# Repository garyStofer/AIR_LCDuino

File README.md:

# AIR_LCDuino
~Uino based LCD display instrument to indicate Atmosphere and Wind related measurements. 

This Arduino-IDE based project is for a simple Air-data display (Weather station) display based on a custom ATMEGA 328P based PCB which incorporates a standard 8x2 LCD (HD44780) and a rotary knob to select the various readings and settings. 

The sensors used are the Air-data and Wind sensors from the Wunder-Weather-Station project and can be found here [http://wws.us.to](http://wws.us.to)

The EagleCAD files for the PCB can be found in the hardware folder. The base PCB can be ordered from OSH PCB by searching for [Air_LCDuino](https://oshpark.com/shared_projects/kT6TDwLU) under shared Projects.

The instrument PCB and housing uses a 2.25" standard aircraft round instrument hole pattern. The CAD files for a CNC routed enclosure can be found in the mechanical folder. You will need a copy of CamBam software to open the .cb source file, but the G-code .ngc file should run on most CNC routers with minor modification. There is a .dxf file that shows the basic dims of the PCB and LCD stack-up. 

The following readings are displayed:
- Bus Voltage 
- Density Altitude
- Standard Altitude (Standard Atmosphere)
- Compensated Altitude (by entering current sea level pressure)
- Station Pressure
- Humidity %RH
- Temperature
- Dew point
- Temperature Dewpt. Spread 
- Wind Direction
- Wind Speed current ( 1 second)
- Wind Average (10 minutes running average)
- Wind Gust ( last 10 minutes )

The two LEDs indicate alarm situations 

Blue LED comes on when Temp <= 1deg C
Red LED comes on when Vbus is < 11 or >15 volt 
Red LED comes on when Temp-Dewpt spread is <8 deg F

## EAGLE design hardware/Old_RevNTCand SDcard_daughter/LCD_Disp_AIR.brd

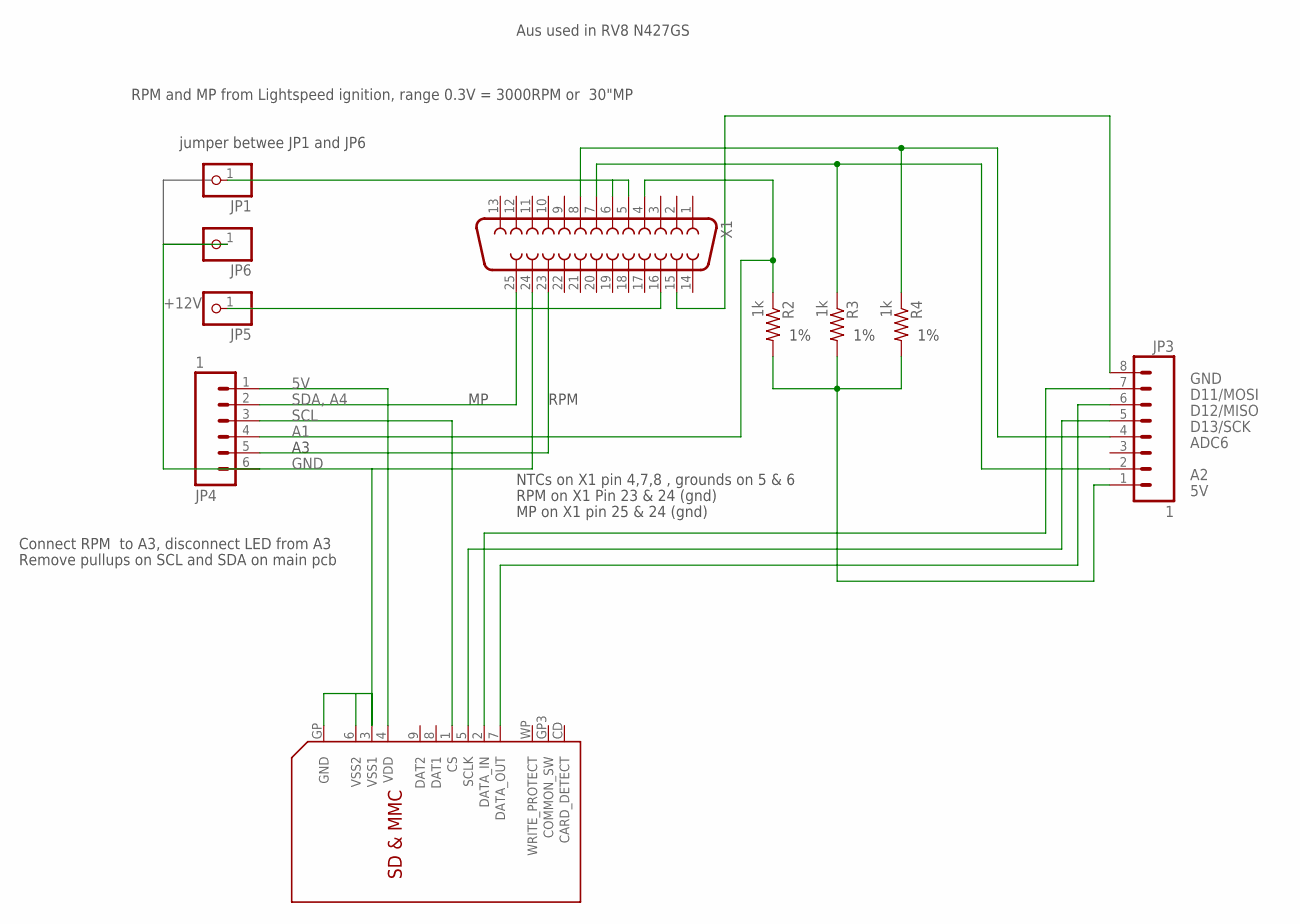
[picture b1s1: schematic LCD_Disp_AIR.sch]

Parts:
JP1, JP6: PINHD-1X1CB; 1X01-CLEANBIG
JP3: 1; 1X08
JP4: 1; 1X06
JP5: PINHD-1X1; 1X01
R2, R3, R4: 1k; 0204/7
U$1: SDMMC06132; 06132
X1: DB25_FEMALEVB; F25VB

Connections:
+12V: JP5.1, X1.16
GND: JP4.6, JP6.1, U$1.3 (VSS1), U$1.6 (VSS2), U$1.GP (GND), X1.24
MISO: JP3.6, U$1.7 (DATA_OUT)
MOSI: JP3.7, U$1.2 (DATA_IN)
unnamed: JP1.1, X1.5, X1.6
unnamed: JP3.1, R2.2, R3.2, R4.2
unnamed: JP3.8, X1.15
unnamed: JP4.5, X1.23
unnamed: JP4.2, X1.25
unnamed: JP3.2, R3.1, X1.7
unnamed: JP3.4, R4.1, X1.8
unnamed: JP4.4, R2.1, X1.4
SCI_SD_SS: JP4.3, U$1.1 (CS)
SCLK: JP3.5, U$1.5 (SCLK)
VDD: JP4.1, U$1.4 (VDD)

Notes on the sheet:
SDA, A4
SCL
GND
ADC6
D13/SCK
D12/MISO
D11/MOSI
jumper betwee JP1 and JP6
Connect RPM to A3, disconnect LED from A3
Remove pullups on SCL and SDA on main pcb
RPM
RPM and MP from Lightspeed ignition, range 0.3V = 3000RPM or 30"MP
Aus used in RV8 N427GS
NTCs on X1 pin 4,7,8 , grounds on 5 & 6
RPM on X1 Pin 23 & 24 (gnd)
MP on X1 pin 25 & 24 (gnd)

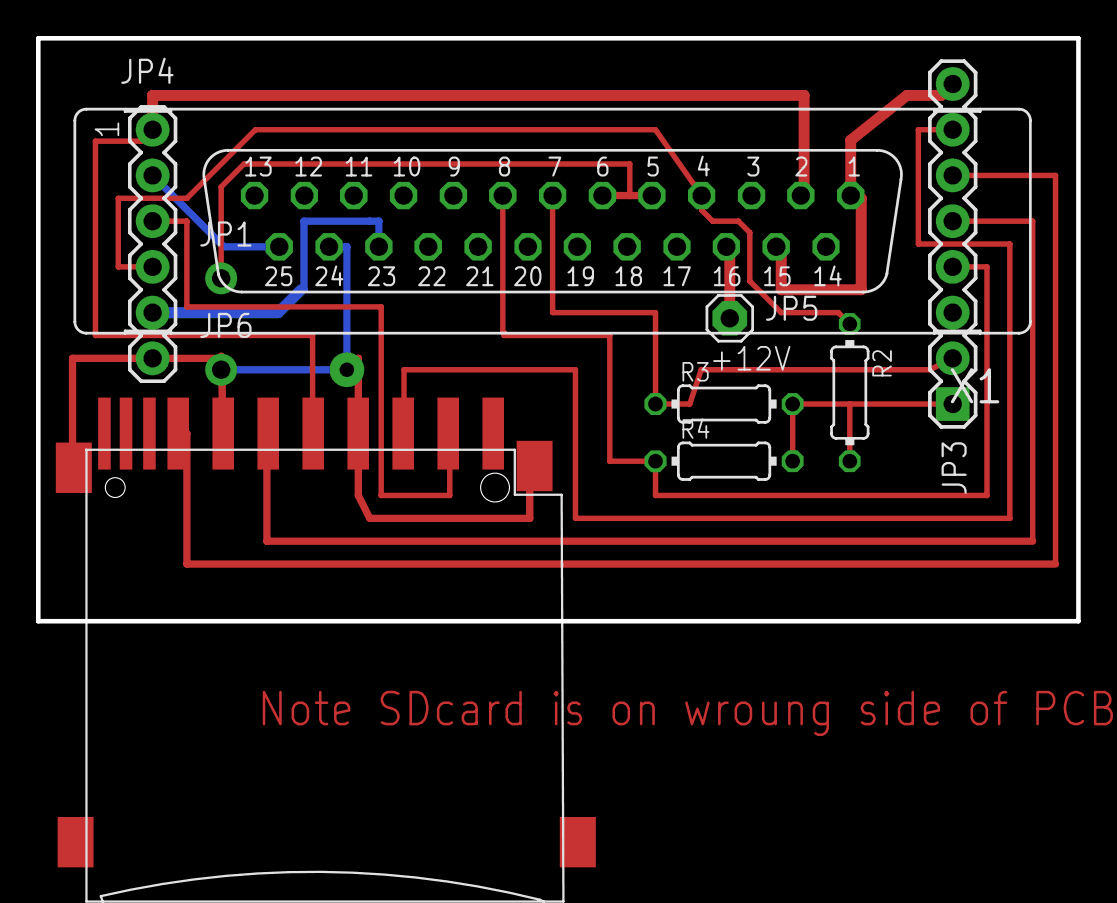
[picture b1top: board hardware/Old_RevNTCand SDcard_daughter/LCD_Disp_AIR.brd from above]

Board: 2 copper layers, 57.8 x 32.4 mm, 10 parts (0 on the bottom side), 15 nets.

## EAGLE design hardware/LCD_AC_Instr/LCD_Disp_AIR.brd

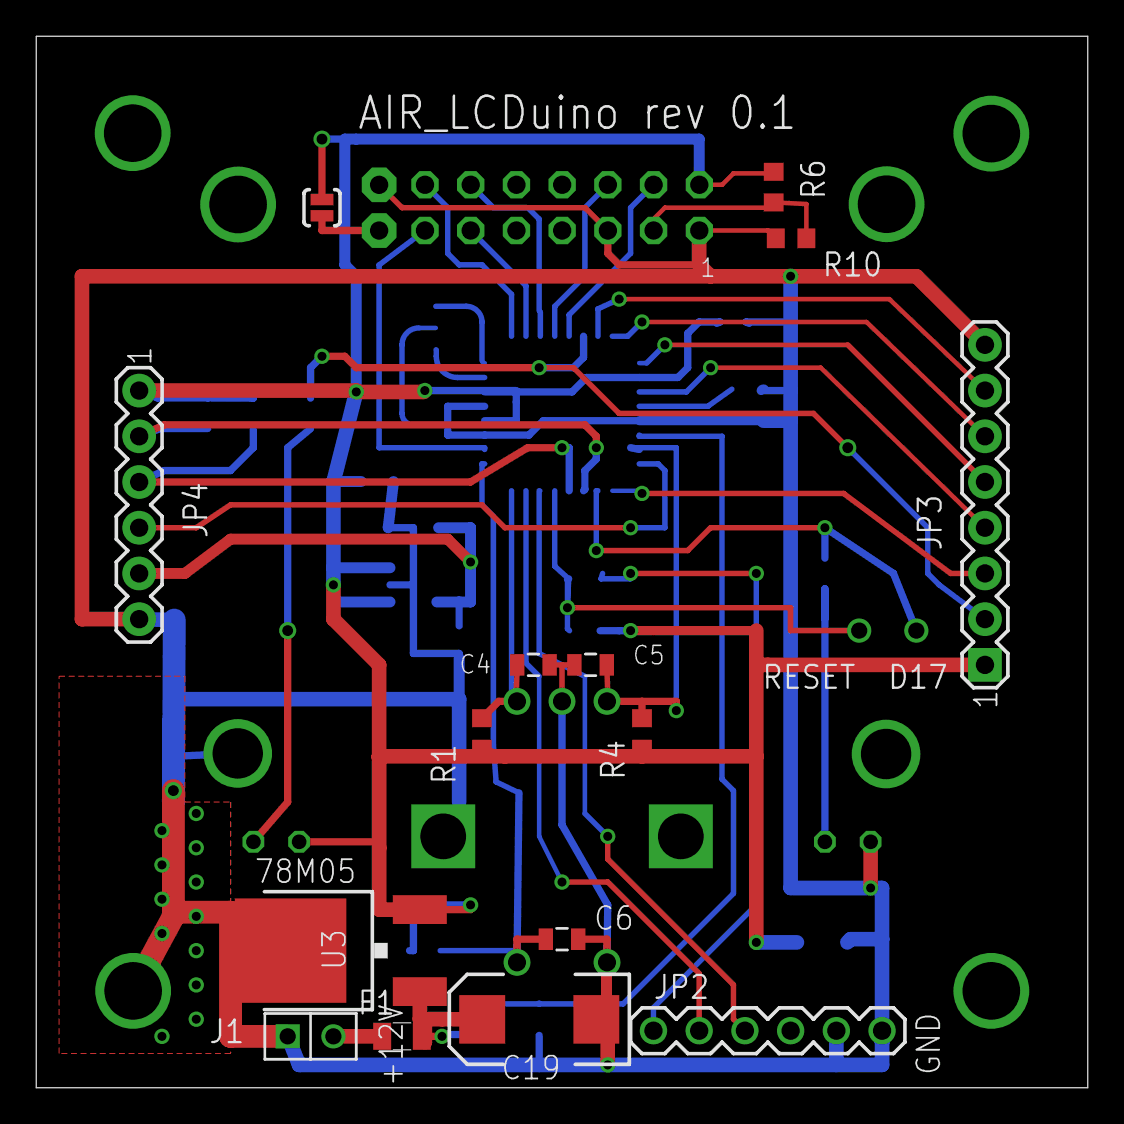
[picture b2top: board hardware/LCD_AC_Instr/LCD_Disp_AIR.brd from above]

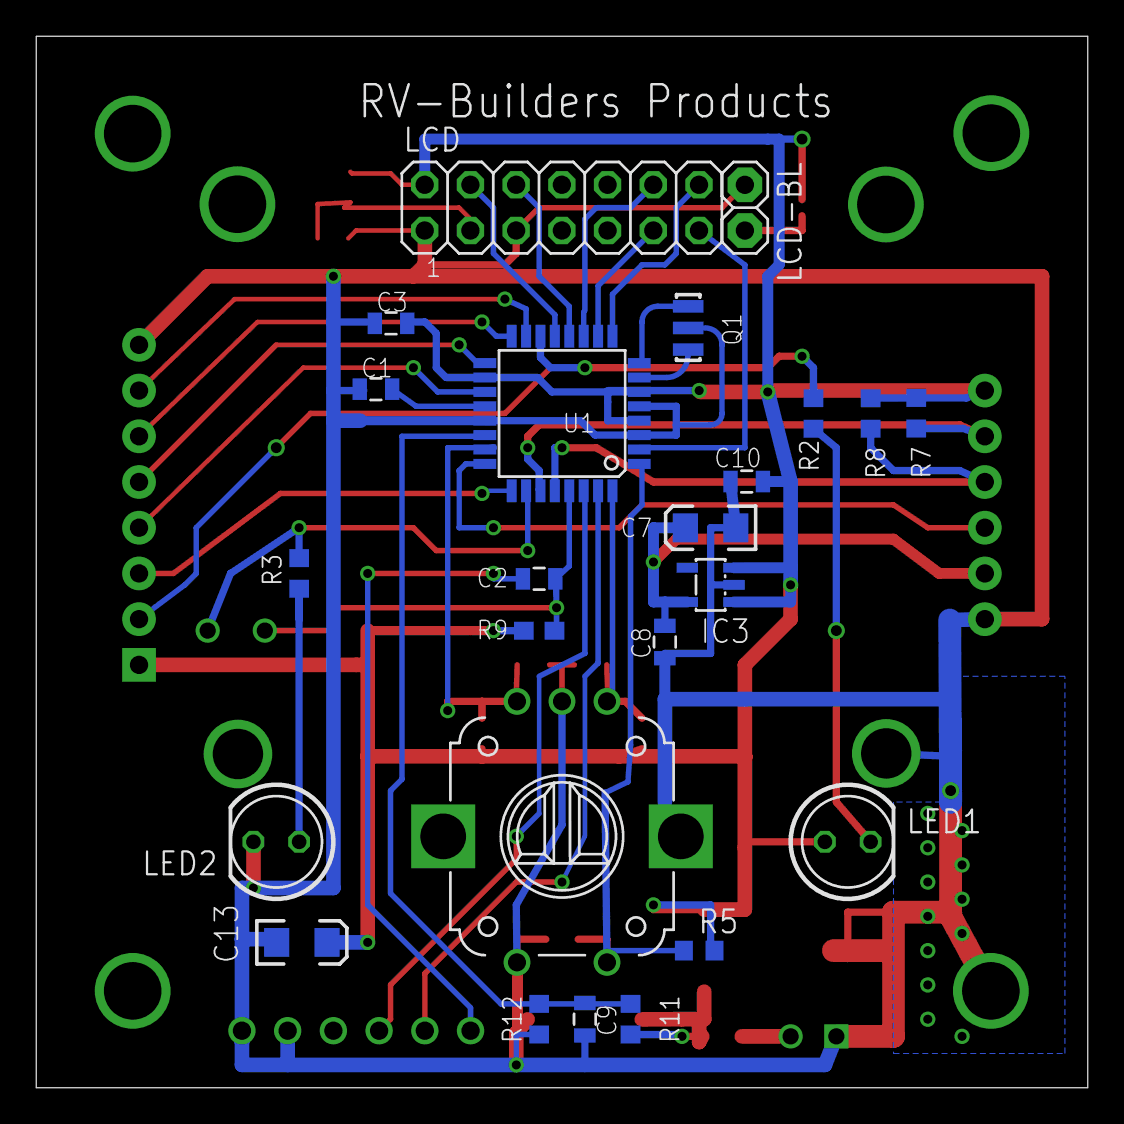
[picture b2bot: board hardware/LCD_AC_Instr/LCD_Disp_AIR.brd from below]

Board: 2 copper layers, 58.4 x 58.4 mm, 41 parts (24 on the bottom side), 36 nets.

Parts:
C1, C2, C3, C4, C5, C6, C8, C9, C10: 0.1uF; 0805
C7, C13: 10uF; EIA3216
C19: 10uF; EIA7343
D17: D17-A3-PC3; P1-13
F1: 4A; PTC0805
IC3: TC10553.3V; SOT23-5
J1: 12V input; M1X2
JP2: 5V UART; 1X06
JP3: 1; 1X08
JP4: 1; 1X06
LCD: LCD; 2X07
LCD-BL: 1X02
LED1, LED2: LED-5MM
Q1: 16MHz; RESONATOR-SMD
R1, R4, R5: 10k; R603
R2, R3: 470; R603
R6: R603
R7, R8: 100k; R603
R9: 10K; 0603
R10: 120; R603
R11: 14K; R603
R12: 6.8K; R603
RESET: SOLDER_POINTA; P1-13
SJ1: BACKLIGHT; SJ_2S-NO
SW1: ENCODER_SW1-PEC12; PEC12_INCREMENTAL_ENCODER
U1: ATMEGA328P-AU(R); TQFP32-08
U3: 78M05; DPACK

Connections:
5V: C3.2, C10.1, C13.A, IC3.1, IC3.3, JP3.1, JP4.1, LCD.2, LED1.A, R1.2, R4.1, R5.2, R6.2, R7.1, R8.1, R9.2, SJ1.1, U1.4, U1.6, U1.18, U3.3
12V_INPUT: C19.A, F1.2, R11.2, U3.1
A0_PC0: C5.2, R4.2, SW1.B, U1.23
A1_PC1: JP4.4, U1.24
A2_PC2: JP3.3, U1.25
A3_PC3: D17.1, R3.2, U1.26
A4_PC4_SDA: JP4.2, R7.2, U1.27
A5_PC5_SCL: JP4.3, R8.2, U1.28
ADC6: JP3.4, U1.19
ADC7: C9.1, R11.1, R12.2, U1.22
AREF: C1.2, U1.20
D2_PD2(INT0): C4.2, R1.1, SW1.A, U1.32
D3_PD3(INT1): C6.2, R5.1, SW1.P1, U1.1
D4_PD4: LCD.13, U1.2
D5_PD5: LCD.14, U1.9
D6_PD6: LCD.11, U1.10
D7_PD7: LCD.12, U1.11
D8_PB0: LCD.6, U1.12
D9_PB1: LCD.4, U1.13
D10_PB2_SS: JP3.2, R2.2, U1.14
D11_PB3_MOSI: JP3.7, U1.15
D12_PB4_MISO: JP3.6, U1.16
D13_PB5_SCK: JP3.5, U1.17
GND: C1.1, C3.1, C4.1, C5.1, C6.1, C7.C, C8.2, C9.2, C10.2, C13.C, C19.C, IC3.2, J1.1, JP2.5, JP2.6, JP3.8, JP4.6, LCD.1, LCD.5, LCD-BL.1, LED2.K, Q1.2, R10.1, R12.1, SW1.C, SW1.P2, U1.3, U1.5, U1.21, U3.4
unnamed: LCD.3, R6.1, R10.2
unnamed: Q1.1, U1.8
unnamed: C2.2, JP2.1
unnamed: Q1.3, U1.7
unnamed: F1.1, J1.2
unnamed: LED1.K, R2.1
unnamed: LCD-BL.2, SJ1.2
unnamed: LED2.A, R3.1
RESET: C2.1, R9.1, RESET.1, U1.29
RXI: JP2.3, U1.30
TXO: JP2.2, U1.31
V3_3V: C7.A, C8.1, IC3.5, JP4.5

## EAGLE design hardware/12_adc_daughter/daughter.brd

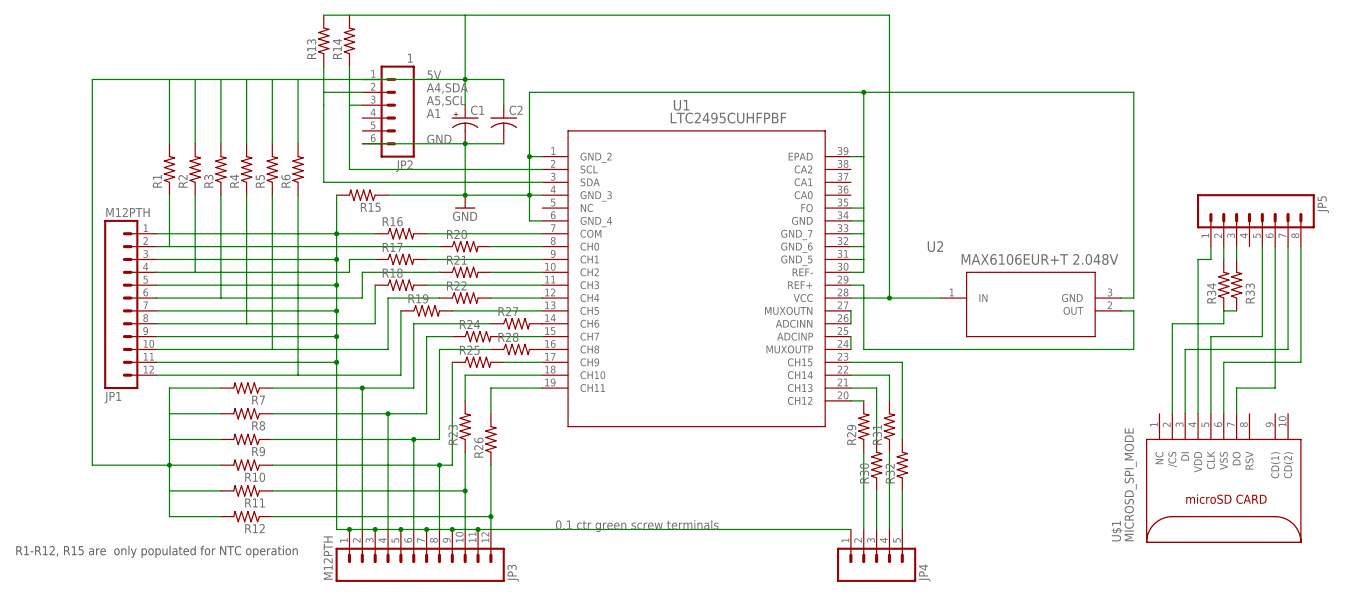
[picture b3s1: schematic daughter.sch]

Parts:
C1: CPOL-USSMCB; SMC_B
C2: C-USC0805; C0805
JP1, JP3: M12PTH; 1X12
JP2: 1; 1X06
JP4: M05PTH; 1X05
JP5: M081X08; 1X08
R1, R2, R3, R4, R5, R6, R7, R8, R9, R10, R11, R12, R13, R14, R15, R16, R17, R18, R19, R20, R21, R22, R23, R24, R25, R26, R27, R28, R29, R30, R31, R32, R33, R34: R-US_R0603; R0603
U1: LTC2495CUHFPBF; QFN-38_UHF
U2: MAX6106EUR+T 2.048V; 21-0051H
U$1: MICROSD_SPI_MODE; MICRO_SD_CONNECTOR

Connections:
GND: C1.-, C2.2, JP2.6, R15.1, U1.1 (GND_2), U1.4 (GND_3), U1.6 (GND_4), U1.30 (REF-), U1.31 (GND_5), U1.32 (GND_6), U1.33 (GND_7), U1.34 (GND), U1.35 (FO), U1.39 (EPAD), U2.3 (GND)
unnamed: JP1.2, R1.1, R20.1
unnamed: JP1.1, JP1.3, JP1.5, JP1.7, JP1.9, JP1.11, JP3.1, JP3.3, JP3.5, JP3.7, JP3.9, JP3.11, JP4.1, R15.2, R16.1
unnamed: JP1.4, R2.1, R17.1
unnamed: JP1.6, R3.1, R21.1
unnamed: JP5.5, U$1.5 (CLK)
unnamed: JP1.8, R4.1, R18.1
unnamed: JP1.10, R5.1, R22.1
unnamed: JP1.12, R6.1, R19.1
unnamed: JP3.2, R7.1, R27.1
unnamed: JP3.4, R8.1, R24.1
unnamed: JP3.6, R9.1, R28.1
unnamed: JP3.8, R10.1, R25.1
unnamed: JP3.10, R11.1, R23.1
unnamed: JP3.12, R12.1, R26.1
unnamed: U1.26 (ADCINN), U1.27 (MUXOUTN)
unnamed: C1.+, C2.1, JP2.1, R1.2, R2.2, R3.2, R4.2, R5.2, R6.2, R7.2, R8.2, R9.2, R10.2, R11.2, R12.2, R13.2, R14.2, U1.28 (VCC), U2.1 (IN)
unnamed: U1.24 (MUXOUTP), U1.25 (ADCINP)
unnamed: R20.2, U1.8 (CH0)
unnamed: JP2.2, R13.1, U1.3 (SDA)
unnamed: JP2.3, R14.1, U1.2 (SCL)
unnamed: R32.2, U1.23 (CH15)
unnamed: R31.2, U1.22 (CH14)
unnamed: R30.2, U1.21 (CH13)
unnamed: R29.2, U1.20 (CH12)
unnamed: R17.2, U1.9 (CH1)
unnamed: U1.29 (REF+), U2.2 (OUT)
unnamed: R22.2, U1.12 (CH4)
unnamed: R21.2, U1.10 (CH2)
unnamed: R27.2, U1.14 (CH6)
unnamed: R18.2, U1.11 (CH3)
unnamed: R19.2, U1.13 (CH5)
unnamed: R24.2, U1.15 (CH7)
unnamed: R28.2, U1.16 (CH8)
unnamed: R25.2, U1.17 (CH9)
unnamed: R23.2, U1.18 (CH10)
unnamed: R26.2, U1.19 (CH11)
unnamed: JP4.3, R30.1
unnamed: JP4.5, R32.1
unnamed: JP4.2, R29.1
unnamed: JP4.4, R31.1
unnamed: R16.2, U1.7 (COM)
unnamed: R33.1, R34.1, U$1.2 (/CS)
unnamed: JP5.7, U$1.3 (DI)
unnamed: JP5.6, U$1.7 (DO)
unnamed: JP5.8, U$1.6 (VSS)
unnamed: JP5.1, U$1.4 (VDD)
unnamed: JP5.3, R33.2
unnamed: JP5.2, R34.2

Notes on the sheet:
A4,SDA
A5,SCL
GND
0.1 ctr green screw terminals
R1-R12, R15 are only populated for NTC operation

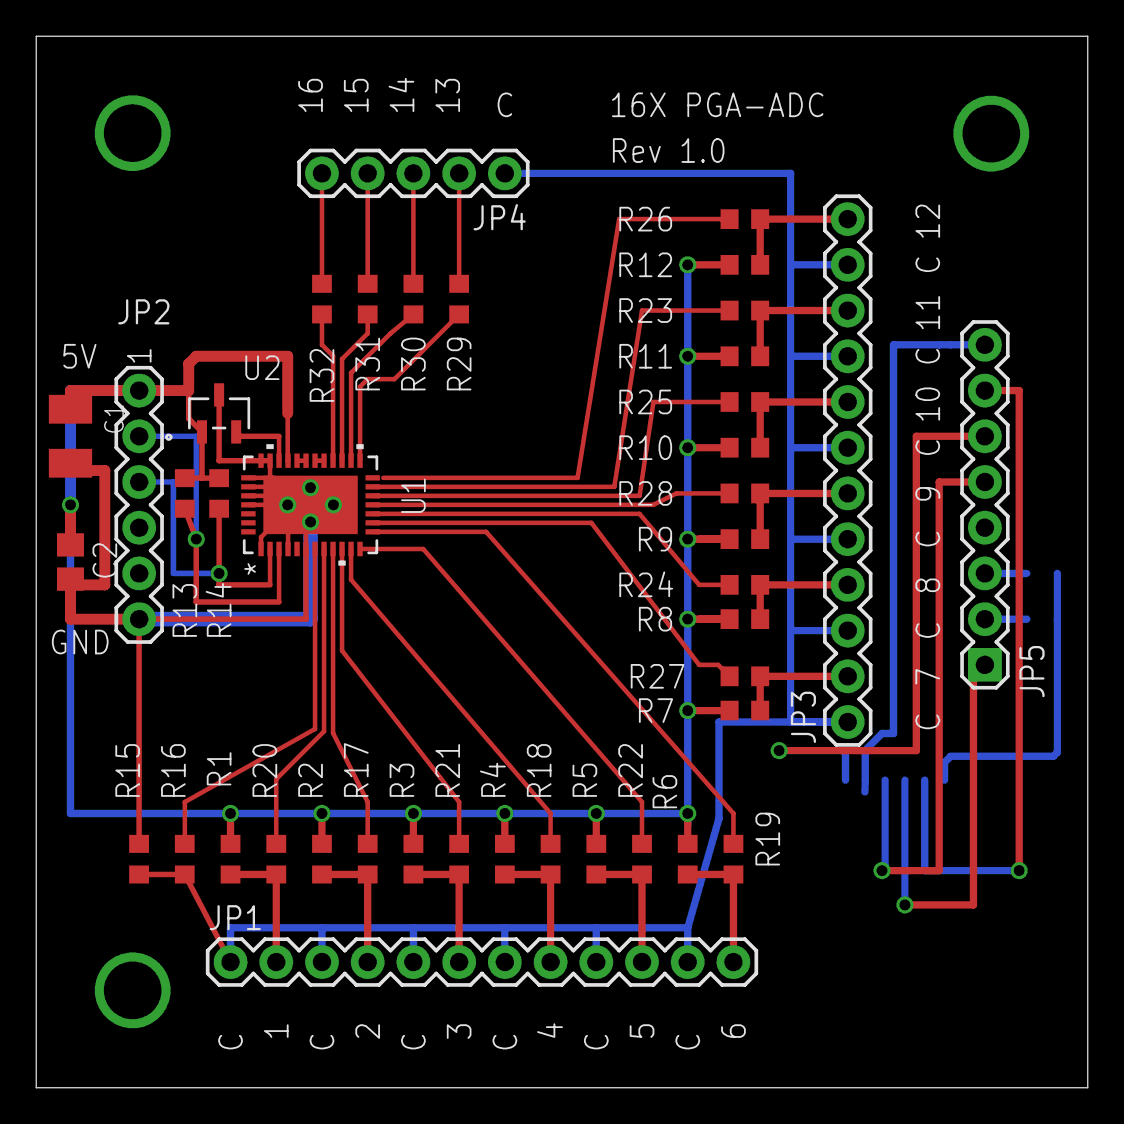
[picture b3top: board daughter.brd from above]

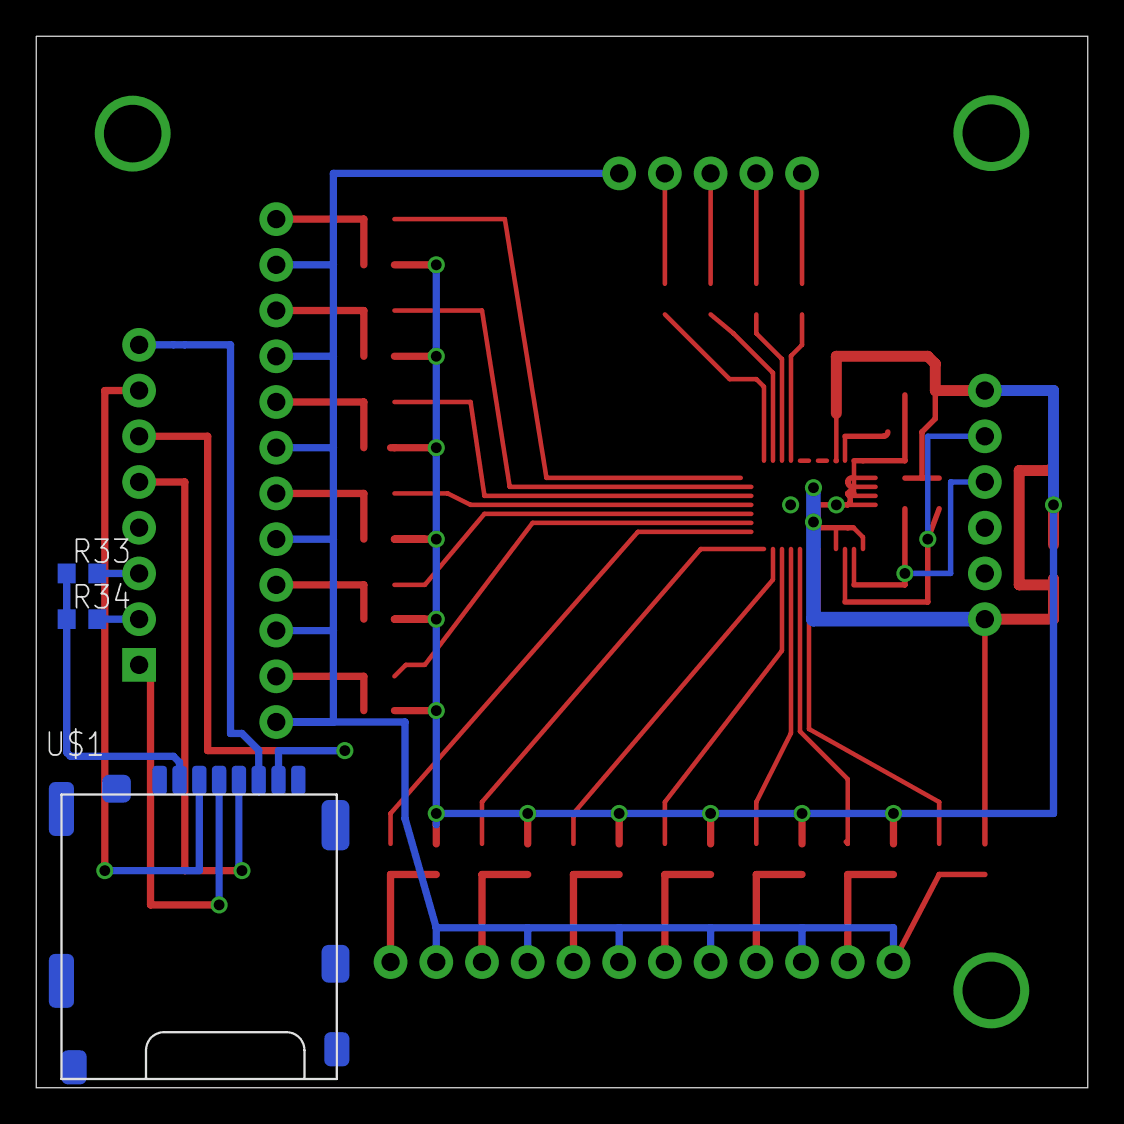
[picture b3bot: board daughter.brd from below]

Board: 2 copper layers, 58.4 x 58.4 mm, 44 parts (3 on the bottom side), 49 nets.

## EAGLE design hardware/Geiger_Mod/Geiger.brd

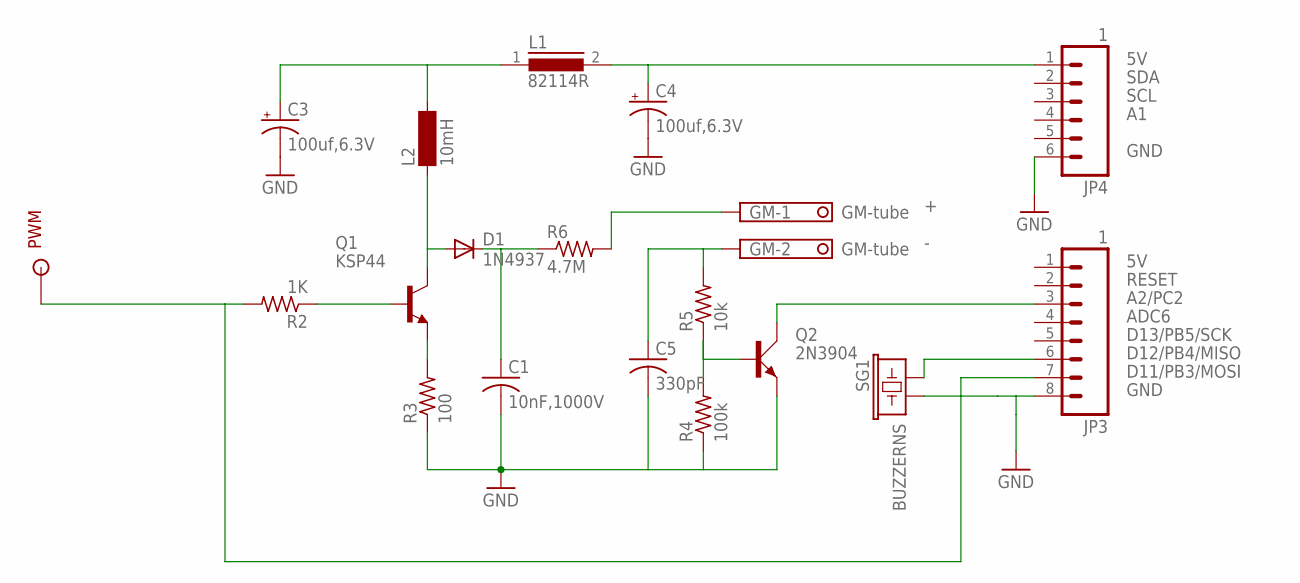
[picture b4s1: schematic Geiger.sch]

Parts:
C1: 10nF,1000V; C150-054X183
C3, C4: 100uf,6.3V; E2,5-7
C5: 330pF; C050-045X075
D1: 1N4937; DO41-10
GM: GM-tube; 1751248
JP3: 1; 1X08
JP4: 1; 1X06
L1: 82114R
L2: 10mH; BS11
PWM: SOLDER_POINTA; P1-13
Q1: KSP44; TO92-EBC
Q2: 2N3904; TO92D
R2: 1K; 0207/10
R3: 100; 0207/10
R4: 100k; 0207/10
R5: 10k; 0207/10
R6: 4.7M; 0207/10
SG1: BUZZERNS; BUZZER-12MM-NS

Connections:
+5V: C4.+, JP4.1, L1.2
GND: C1.2, C3.-, C4.-, C5.2, JP3.8, JP4.6, Q2.E, R3.1, R4.1, SG1.- (2)
unnamed: JP3.7, PWM.1, R2.2
unnamed: Q1.B, R2.1
unnamed: JP3.6, SG1.+ (1)
unnamed: Q1.E, R3.2
unnamed: D1.A, L2.1, Q1.C
unnamed: C1.1, D1.C, R6.1
unnamed: GM.1, R6.2
unnamed: Q2.B, R4.2, R5.1
unnamed: C3.+, L1.1, L2.2
unnamed: C5.1, GM.2, R5.2
RESET: JP3.3, Q2.C

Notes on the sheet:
SDA
SCL
GND
A2/PC2
ADC6
D13/PB5/SCK
D12/PB4/MISO
D11/PB3/MOSI

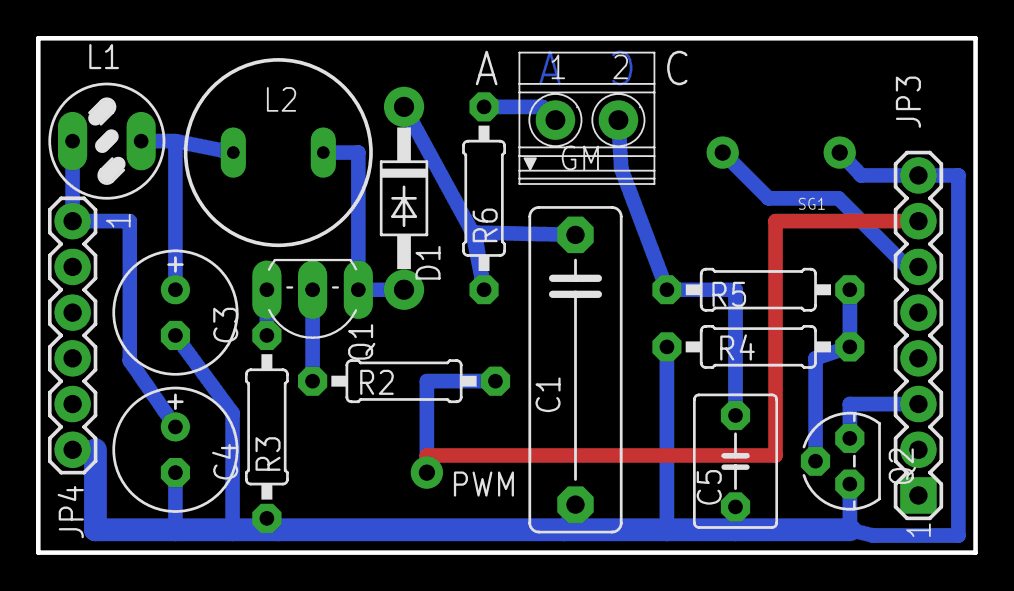
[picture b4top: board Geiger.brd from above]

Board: 2 copper layers, 52.1 x 28.6 mm, 19 parts (0 on the bottom side), 13 nets.

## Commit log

2015-11-12 Arduino based air data sensor and display.
2015-11-12 added readme text
2015-11-12 added pics
2015-11-12 added PCB and enclosure CNC files
2015-11-18 updated the mechanical drawings Debugged i2C hardware problem with old Bosch Barometer not being 5V tolerant. Some code changes related to above.
2015-11-19 moved Altimeter setting menu into Barometer file added wind vane offset entry to wind direction setup added wet bulb readout feature.
2015-11-19 changed resistor value in i2C lines to 100K to allow for the old style BMP085 which is not 5V compatible
2016-01-13 Added TMP100 temperature sensor.
2016-02-02 added support for TMP100 temperature sensor added WetBulb temp readout added wind direction and speed readout with calibration feature added Metric/Imperial display feature added RMP display feature 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
2016-02-03 Fixed RPM calculation
2016-03-18 Added Geiger counter schematic and layout Added copy arduino sketch from rhelectronics
2016-03-21 layout changes
2016-03-21 removed Geiger mod from this repository -- moved into its own
2016-12-13 added instruction text for burning bootloader via AVR_JTAGICE MK2
2016-12-13 added instruction text for burning boot loader via AVR_JTAGICE MK2
2016-12-13 added space in file for testing of branching
2016-12-15 added dwg file
2017-09-23 added 12_adc_daughter/LTC2495_16x_pga_adc.pdf removed eagle.epf files and added gitignore file
2017-09-27 added app note from LTC
2018-10-30 fixed spelling, added data sheets
2018-10-30 added schematic for use as solder controller
2020-02-12 Added Fuel pressure reading and external alarm output to 3x Oil NTC temp instrument fixed schematics for incorrect pinout on X1 connector

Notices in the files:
parts and their libraries:
SparkFun-Connectors: Licensing: CC v3.0 Share-Alike You are welcome to use this library for commercial purposes.
SparkFun-Retired: Licensing: Creative Commons ShareAlike 4.0 International - https://creativecommons.org/licenses/by-sa/4.0
